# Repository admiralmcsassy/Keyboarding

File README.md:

# Keyboarding
Custom Mechanical Keyboards

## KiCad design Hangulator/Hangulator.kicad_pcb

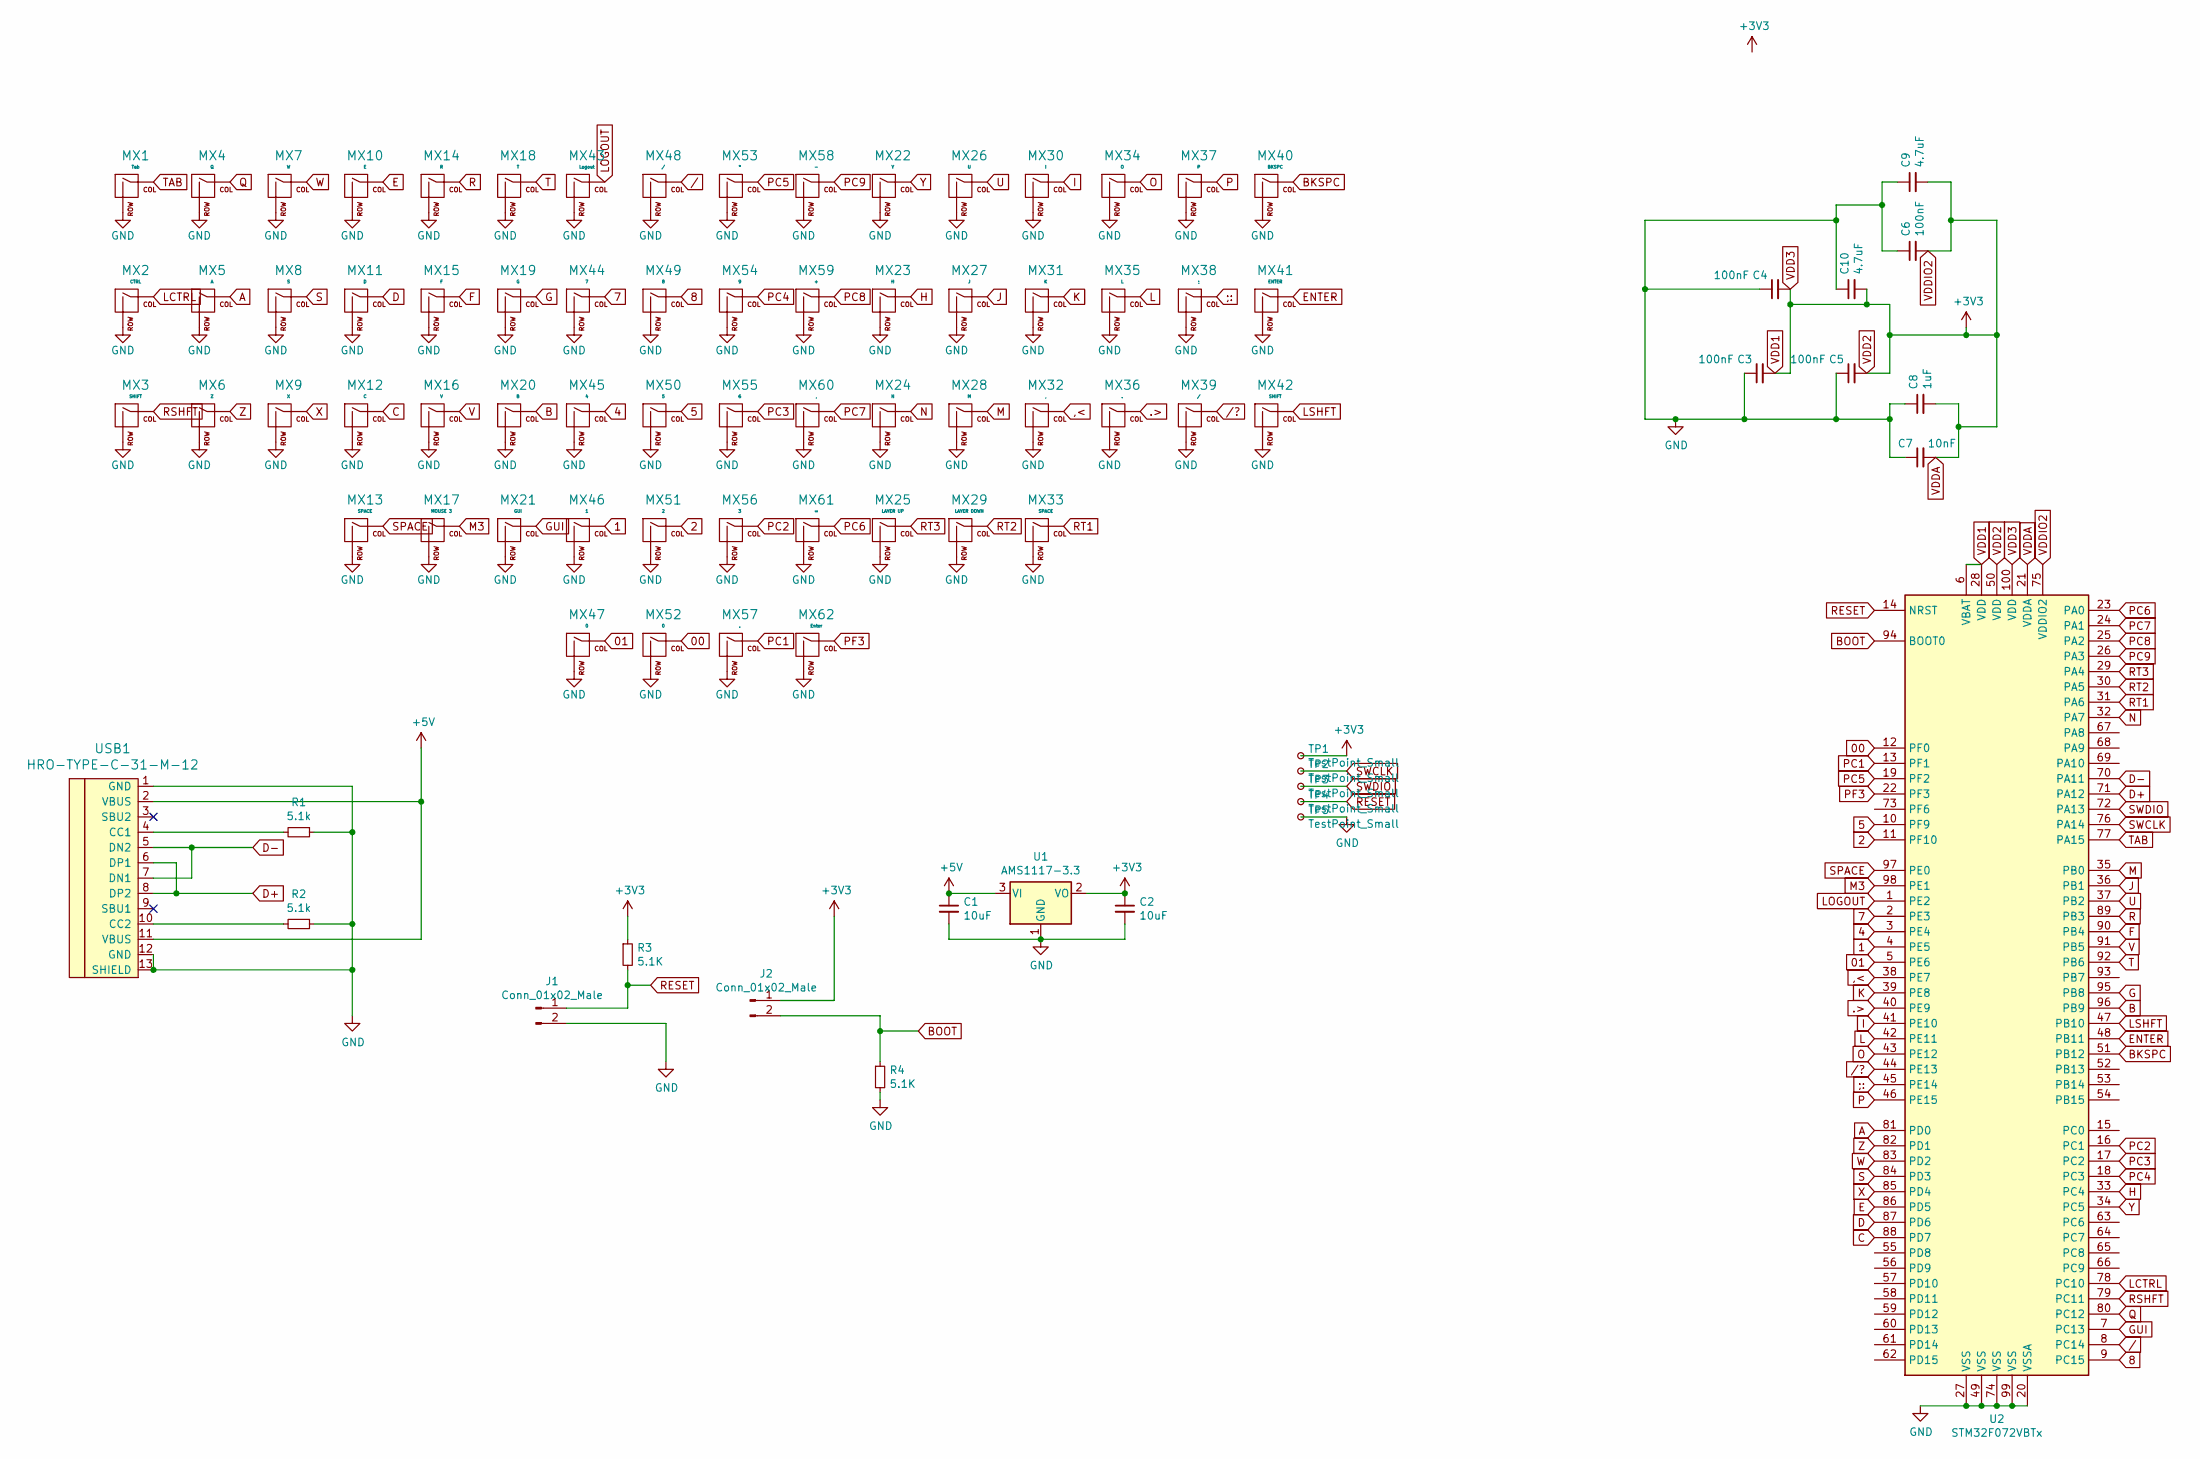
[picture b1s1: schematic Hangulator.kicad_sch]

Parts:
C1, C2: 10uF; C_0805_2012Metric_Pad1.18x1.45mm_HandSolder
C3, C4, C5, C6: 100nF; C_0805_2012Metric_Pad1.18x1.45mm_HandSolder
C7: 10nF; C_0805_2012Metric_Pad1.18x1.45mm_HandSolder
C8: 1uF; C_0805_2012Metric_Pad1.18x1.45mm_HandSolder
C9, C10: 4.7uF; C_0603_1608Metric_Pad1.08x0.95mm_HandSolder
J1, J2: Conn_01x02_Male; D_0805_2012Metric_Pad1.15x1.40mm_HandSolder
MX1: Tab; MX-1U-NoLED
MX2: CTRL; MX-1U-NoLED
MX3, MX42: SHIFT; MX-1U-NoLED
MX4: Q; MX-1U-NoLED
MX5: A; MX-1U-NoLED
MX6: Z; MX-1U-NoLED
MX7: W; MX-1U-NoLED
MX8: S; MX-1U-NoLED
MX9: X; MX-1U-NoLED
MX10: E; MX-1U-NoLED
MX11: D; MX-1U-NoLED
MX12: C; MX-1U-NoLED
MX13, MX33: SPACE; MX-1U-NoLED
MX14: R; MX-1U-NoLED
MX15: F; MX-1U-NoLED
MX16: V; MX-1U-NoLED
MX17: MOUSE 3; MX-1U-NoLED
MX18: T; MX-1U-NoLED
MX19: G; MX-1U-NoLED
MX20: B; MX-1U-NoLED
MX21: GUI; MX-1U-NoLED
MX22: Y; MX-1U-NoLED
MX23: H; MX-1U-NoLED
MX24: N; MX-1U-NoLED
MX25: LAYER UP; MX-1U-NoLED
MX26: U; MX-1U-NoLED
MX27: J; MX-1U-NoLED
MX28: M; MX-1U-NoLED
MX29: LAYER DOWN; MX-1U-NoLED
MX30: I; MX-1U-NoLED
MX31: K; MX-1U-NoLED
MX32, MX60: ,; MX-1U-NoLED
MX34: O; MX-1U-NoLED
MX35: L; MX-1U-NoLED
MX36, MX57: .; MX-1U-NoLED
MX37: P; MX-1U-NoLED
MX38: ;; MX-1U-NoLED
MX39, MX48: /; MX-1U-NoLED
MX40: BKSPC; MX-1U-NoLED
MX41: ENTER; MX-1U-NoLED
MX43: Logout; MX-1U-NoLED
MX44: 7; MX-1U-NoLED
MX45: 4; MX-1U-NoLED
MX46: 1; MX-1U-NoLED
MX47, MX52: 0; MX-1U-NoLED
MX49: 8; MX-1U-NoLED
MX50: 5; MX-1U-NoLED
MX51: 2; MX-1U-NoLED
MX53: *; MX-1U-NoLED
MX54: 9; MX-1U-NoLED
MX55: 6; MX-1U-NoLED
MX56: 3; MX-1U-NoLED
MX58: -; MX-1U-NoLED
MX59: +; MX-1U-NoLED
MX61: =; MX-1U-NoLED
MX62: Enter; MX-1U-NoLED
R1, R2: 5.1k; R_0805_2012Metric_Pad1.20x1.40mm_HandSolder
R3, R4: 5.1K; R_0805_2012Metric_Pad1.20x1.40mm_HandSolder
TP1, TP2, TP3, TP4, TP5: TestPoint_Small; TestPoint_Pad_D1.0mm
U1: AMS1117-3.3; SOT-223-3_TabPin2
U2: STM32F072VBTx; LQFP-100_14x14mm_P0.5mm
USB1: HRO-TYPE-C-31-M-12; HRO-TYPE-C-31-M-12-HandSoldering

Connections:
00: MX52.1 (COL), U2.12 (PF0)
1: MX46.1 (COL), U2.4 (PE5)
01: MX47.1 (COL), U2.5 (PE6)
2: MX51.1 (COL), U2.11 (PF10)
4: MX45.1 (COL), U2.3 (PE4)
5: MX50.1 (COL), U2.10 (PF9)
7: MX44.1 (COL), U2.2 (PE3)
8: MX49.1 (COL), U2.9 (PC15)
+5V: C1.1, U1.3 (VI), USB1.2 (VBUS), USB1.11 (VBUS)
,<: MX32.1 (COL), U2.38 (PE7)
.>: MX36.1 (COL), U2.40 (PE9)
;:: MX38.1 (COL), U2.45 (PE14)
A: MX5.1 (COL), U2.81 (PD0)
B: MX20.1 (COL), U2.96 (PB9)
BKSPC: MX40.1 (COL), U2.51 (PB12)
BOOT: J2.2, R4.1, U2.94 (BOOT0)
C: MX12.1 (COL), U2.88 (PD7)
D: MX11.1 (COL), U2.87 (PD6)
D+: U2.71 (PA12), USB1.6 (DP1), USB1.8 (DP2)
D-: U2.70 (PA11), USB1.5 (DN2), USB1.7 (DN1)
E: MX10.1 (COL), U2.86 (PD5)
ENTER: MX41.1 (COL), U2.48 (PB11)
F: MX15.1 (COL), U2.90 (PB4)
G: MX19.1 (COL), U2.95 (PB8)
GND: C1.2, C2.2, C3.1, C4.1, C5.1, C6.1, C7.1, C8.1, C9.1, C10.1, J1.2, MX1.2 (ROW), MX2.2 (ROW), MX3.2 (ROW), MX4.2 (ROW), MX5.2 (ROW), MX6.2 (ROW), MX7.2 (ROW), MX8.2 (ROW), MX9.2 (ROW), MX10.2 (ROW), MX11.2 (ROW), MX12.2 (ROW), MX13.2 (ROW), MX14.2 (ROW), MX15.2 (ROW), MX16.2 (ROW), MX17.2 (ROW), MX18.2 (ROW), MX19.2 (ROW), MX20.2 (ROW), MX21.2 (ROW), MX22.2 (ROW), MX23.2 (ROW), MX24.2 (ROW), MX25.2 (ROW), MX26.2 (ROW), MX27.2 (ROW), MX28.2 (ROW), MX29.2 (ROW), MX30.2 (ROW), MX31.2 (ROW), MX32.2 (ROW), MX33.2 (ROW), MX34.2 (ROW), MX35.2 (ROW), MX36.2 (ROW), MX37.2 (ROW), MX38.2 (ROW), MX39.2 (ROW), MX40.2 (ROW), MX41.2 (ROW), MX42.2 (ROW), MX43.2 (ROW), MX44.2 (ROW), MX45.2 (ROW), MX46.2 (ROW), MX47.2 (ROW), MX48.2 (ROW), MX49.2 (ROW), MX50.2 (ROW), MX51.2 (ROW), MX52.2 (ROW), MX53.2 (ROW), MX54.2 (ROW), MX55.2 (ROW), MX56.2 (ROW), MX57.2 (ROW), MX58.2 (ROW), MX59.2 (ROW), MX60.2 (ROW), MX61.2 (ROW), MX62.2 (ROW), R1.1, R2.1, R4.2, TP5.1, U1.1 (GND), U2.20 (VSSA), U2.27 (VSS), U2.49 (VSS), U2.74 (VSS), U2.99 (VSS), USB1.1 (GND), USB1.12 (GND), USB1.13 (SHIELD)
GUI: MX21.1 (COL), U2.7 (PC13)
H: MX23.1 (COL), U2.33 (PC4)
I: MX30.1 (COL), U2.41 (PE10)
J: MX27.1 (COL), U2.36 (PB1)
K: MX31.1 (COL), U2.39 (PE8)
L: MX35.1 (COL), U2.42 (PE11)
LCTRL: MX2.1 (COL), U2.78 (PC10)
LOGOUT: MX43.1 (COL), U2.1 (PE2)
LSHFT: MX42.1 (COL), U2.47 (PB10)
M: MX28.1 (COL), U2.35 (PB0)
M3: MX17.1 (COL), U2.98 (PE1)
N: MX24.1 (COL), U2.32 (PA7)
unnamed: R1.2, USB1.4 (CC1)
unnamed: R2.2, USB1.10 (CC2)
O: MX34.1 (COL), U2.43 (PE12)
P: MX37.1 (COL), U2.46 (PE15)
PC1: MX57.1 (COL), U2.13 (PF1)
PC2: MX56.1 (COL), U2.16 (PC1)
PC3: MX55.1 (COL), U2.17 (PC2)
PC4: MX54.1 (COL), U2.18 (PC3)
PC5: MX53.1 (COL), U2.19 (PF2)
PC6: MX61.1 (COL), U2.23 (PA0)
PC7: MX60.1 (COL), U2.24 (PA1)
PC8: MX59.1 (COL), U2.25 (PA2)
PC9: MX58.1 (COL), U2.26 (PA3)
PF3: MX62.1 (COL), U2.22 (PF3)
Q: MX4.1 (COL), U2.80 (PC12)
R: MX14.1 (COL), U2.89 (PB3)
RESET: J1.1, R3.2, TP4.1, U2.14 (NRST)
RSHFT: MX3.1 (COL), U2.79 (PC11)
RT1: MX33.1 (COL), U2.31 (PA6)
RT2: MX29.1 (COL), U2.30 (PA5)
RT3: MX25.1 (COL), U2.29 (PA4)
S: MX8.1 (COL), U2.84 (PD3)
SPACE: MX13.1 (COL), U2.97 (PE0)
SWCLK: TP2.1, U2.76 (PA14)
SWDIO: TP3.1, U2.72 (PA13)
T: MX18.1 (COL), U2.92 (PB6)
TAB: MX1.1 (COL), U2.77 (PA15)
U: MX26.1 (COL), U2.37 (PB2)
V: MX16.1 (COL), U2.91 (PB5)
VDD1: C2.1, C3.2, C4.2, C5.2, C6.2, C7.2, C8.2, C9.2, C10.2, J2.1, R3.1, TP1.1, U1.2 (VO), U2.6 (VBAT), U2.21 (VDDA), U2.28 (VDD), U2.50 (VDD), U2.75 (VDDIO2), U2.100 (VDD)
W: MX7.1 (COL), U2.83 (PD2)
X: MX9.1 (COL), U2.85 (PD4)
Y: MX22.1 (COL), U2.34 (PC5)
Z: MX6.1 (COL), U2.82 (PD1)
/: MX48.1 (COL), U2.8 (PC14)
/?: MX39.1 (COL), U2.44 (PE13)

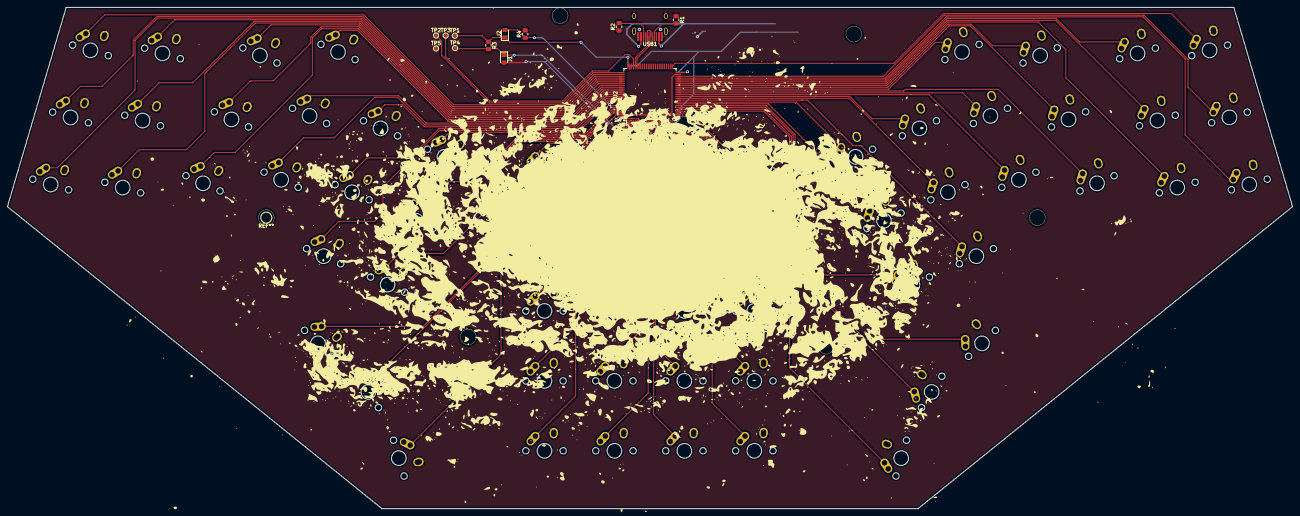
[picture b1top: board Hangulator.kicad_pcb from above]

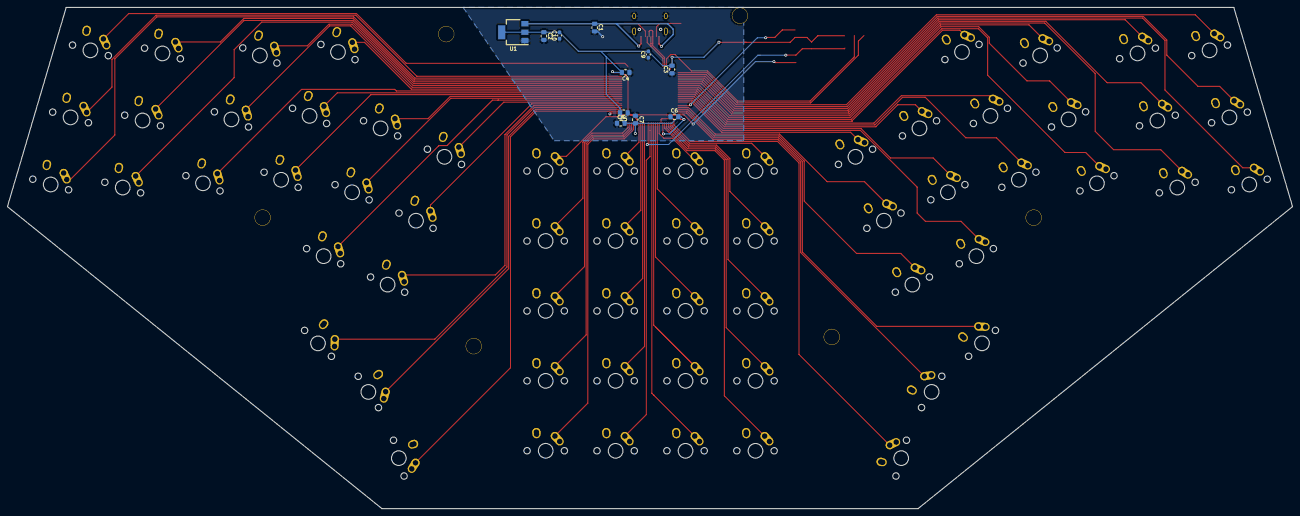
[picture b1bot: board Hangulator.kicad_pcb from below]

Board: 2 copper layers, 350.0 x 136.5 mm, 86 parts (11 on the bottom side), 73 nets.

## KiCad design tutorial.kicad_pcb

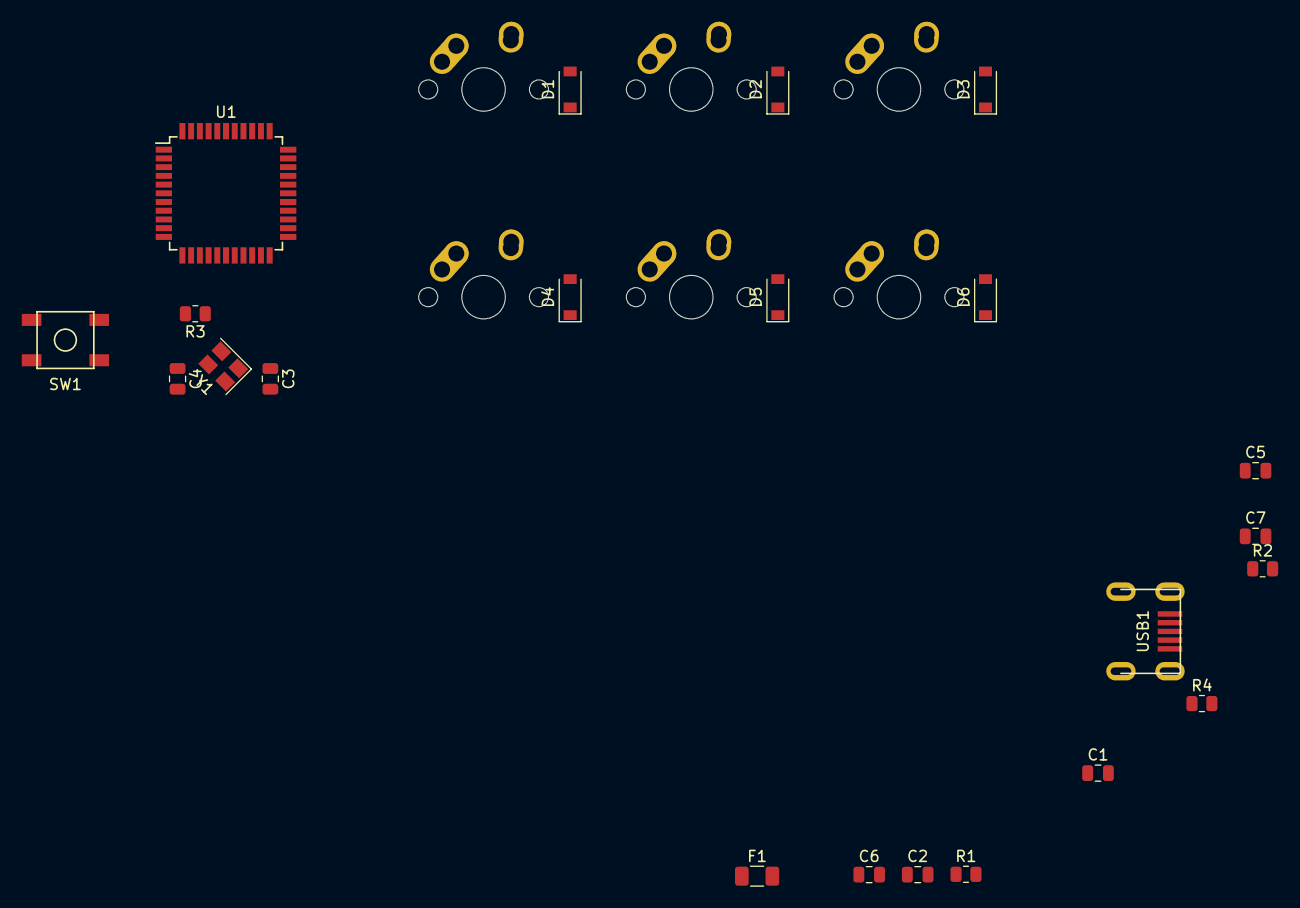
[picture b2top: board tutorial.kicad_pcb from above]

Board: 2 copper layers, 28 parts (0 on the bottom side), 23 nets, no tracks yet.

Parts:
C1, C2, C5: .1uf; C_0805_2012Metric
C3, C4: 22pF; C_0805_2012Metric
C6: 1uf; C_0805_2012Metric
C7: 10uf; C_0805_2012Metric
D1, D2, D3, D4, D5, D6: SOD-123; D_SOD-123
F1: 500mA; Fuse_1206_3216Metric
MX1, MX2, MX3, MX4, MX5, MX6: MX-NoLED; MX-1U-NoLED
R1, R2: 22k; R_0805_2012Metric
R3, R4: 10k; R_0805_2012Metric
SW1: SW_Push; SKQG-1155865
U1: ATmega32U4-AU; TQFP-44_10x10mm_P0.8mm
USB1: Molex-0548190589
Y1: 16MHz; Crystal_SMD_3225-4Pin_3.2x2.5mm

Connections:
+5V: C1.1, C2.1, C5.1, C7.1, F1.1, R3.1, U1.2, U1.7, U1.14, U1.24, U1.34, U1.44
COL0: MX1.1, MX2.1
COL1: MX3.1, MX4.1
COL2: MX5.1, MX6.1
D+: R2.2, USB1.3
D-: R1.2, USB1.4
GND: C1.2, C2.2, C3.2, C4.2, C5.2, C6.2, C7.2, R4.1, SW1.1, U1.5, U1.15, U1.23, U1.35, U1.43, Y1.2, Y1.4
unnamed: C3.1, U1.17, Y1.1
unnamed: C4.1, U1.16, Y1.3
unnamed: C6.1, U1.6
unnamed: D1.2, MX1.2
unnamed: D2.2, MX2.2
unnamed: D3.2, MX3.2
unnamed: D4.2, MX4.2
unnamed: D5.2, MX5.2
unnamed: D6.2, MX6.2
unnamed: R1.1, U1.3
unnamed: R2.1, U1.4
unnamed: R3.2, SW1.2, U1.13
unnamed: R4.2, U1.33
ROW0: D1.1, D3.1, D5.1
ROW1: D2.1, D4.1, D6.1
VCC: F1.2, USB1.5

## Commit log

2021-03-07 Add submodules
2021-03-07 Create sym-lib-table
2021-03-18 started as a split, now its a single, trying to determine whether or not to use the stm32 or atmega32
2021-03-20 Added the Hangulator
2021-03-21 workin it
2021-03-21 Working on it more
2021-03-23 made some more headway
2021-03-23 poop
2021-03-24 slog
2021-03-24 mORE lol
2021-03-24 Done did it now, sent to the man to make
2021-03-24 ho dang
2021-03-24 uuhhhh
2021-03-29 Gettin it hard
2021-04-04 wooohooooo
2021-04-04 dang
2021-04-04 aight.
    wut
2021-04-04 dummm
2021-04-18 getting it done
2021-05-01 more changes
